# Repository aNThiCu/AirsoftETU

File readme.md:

Latest board is very promising , i have semi-abandoned the idea of separating the controls and power components from the sensors. The board is now a 4 layer consisting of GND-3.3V-GND-GND copper pours.
Pcb manufacturing at home sadly cannot fullfill my needs for this project , future versions will not be able to be manufactured in house as i have finished some of the testing needed for a complete product.

This revision still is in no way usable , as i haven't been able to test any of the new software implementations. I just finished the firmware and i am about to go on with assembling the rest of the PCB.
I've been using a board with no power electronics until now for testing the signal complementarity and overall logic of the system.

Hardware changes made from the last readme update:

 - added back the high side pmos , board cannot function without it as freewheel diode would blow
 - added back the mode selector phototransistors and led-added a schmitt trigger for hardware debounce
 - added proper gate drivers , MCP1416T-E
 - added some ESD protection diodes on the gates of the power FETS and 12v power rail
 - moved leds to the 3.3v rail
 - modified shape of PCB for better fitment

Software changes made from the last readme update:
   - configurable duty cycle, not tested actual usable range , over 90% is considered 100% due to dead_time limitations
   - configurable dead time ticks for pwm , 1 tick = 200ns , good for different types of power mosfets
   - implemented synchronous rectification to take the burden off the flywheel diode 
   - changed driving logic to permit both PWM and on/off
   - added burst mode capability
   - changed to platformio

What's coming next:
   - finishing testing with new pcb and firmware
   - troubleshooting indicators, buzzer for quick configs in the upcoming settings tab
   - folder with everything needed for direct manufacturing from a factory
   - might do a different type of trigger , either optical of magnetic , for longevity sake , i like the clicking feel of microswitches more though
   
What's been marked done from last readme update:
   - configurable mode selector switch with multiple modes
   - redo of shape for better fitment in V2 gearboxes

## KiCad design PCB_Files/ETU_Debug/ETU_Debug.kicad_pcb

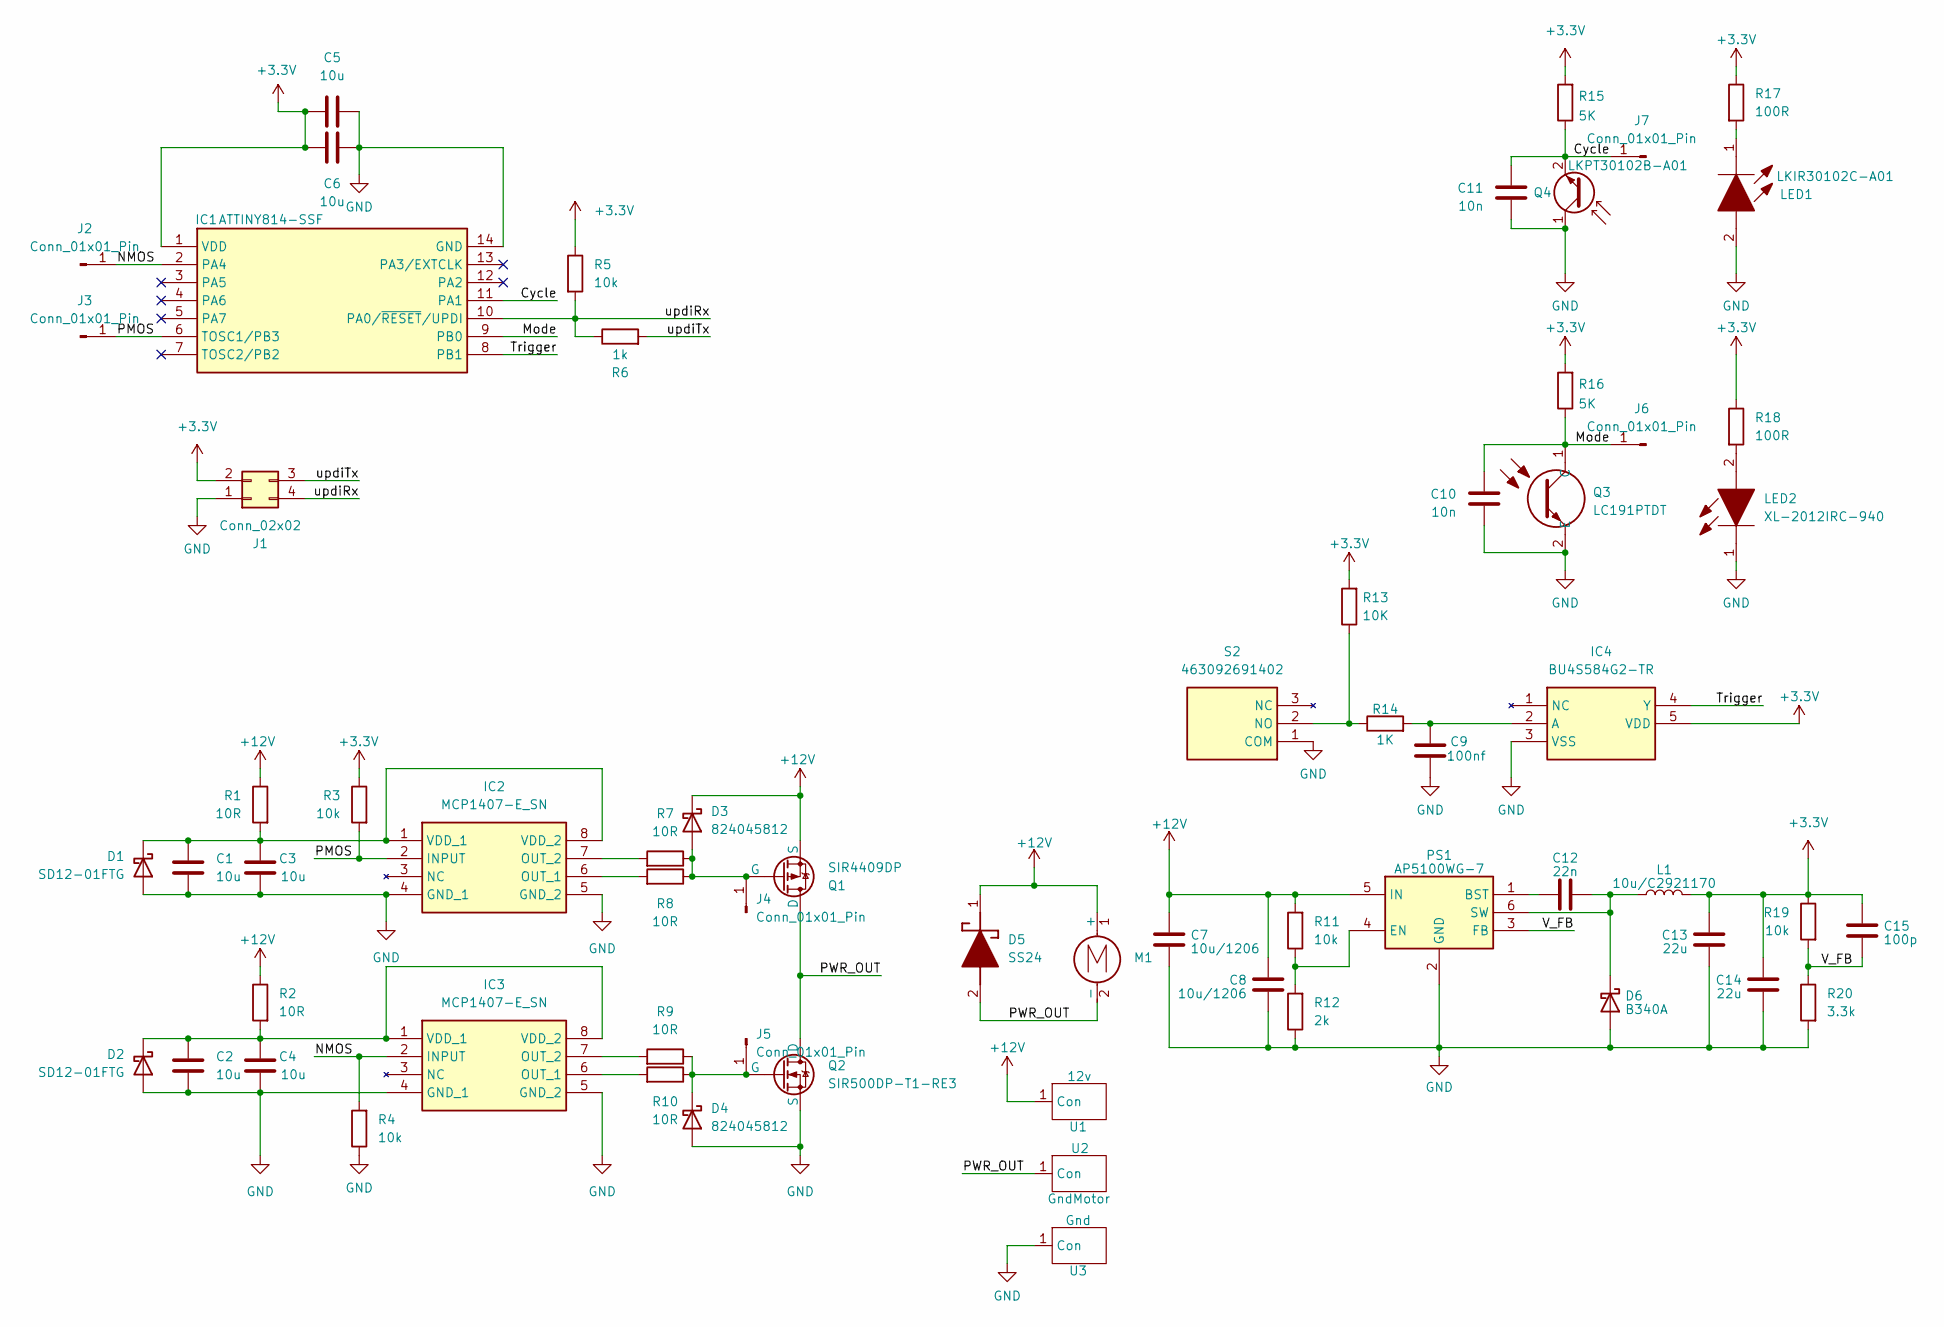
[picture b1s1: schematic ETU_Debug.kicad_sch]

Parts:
C1, C2, C3, C4, C5, C6: 10u; C_0603_1608Metric
C7, C8: 10u/1206; C_0603_1608Metric; MPN C13585
C9: 100nf; C_0603_1608Metric
C10, C11: 10n; C_0603_1608Metric
C12: 22n; C_0603_1608Metric; MPN C21122
C13, C14: 22u; C_0603_1608Metric; MPN C45783
C15: 100p; C_0603_1608Metric; MPN C1790
D1, D2: SD12-01FTG; SOD2613X114N
D3, D4: 824045812
D5: SS24; DIOM5436X247N; Mouser Part Number 821-SS24
D6: B340A; D_SMA; MPN C3018525
IC1: ATTINY814-SSF; SOIC127P600X175-14N; Mouser Part Number 579-ATTINY814-SSF
IC2, IC3: MCP1407-E_SN; SOIC127P600X175-8N; Mouser Part Number 579-MCP1407-E/SN
IC4: BU4S584G2-TR; SOT95P280X125-5N; Mouser Part Number 755-BU4S584G2-TR
J1: Conn_02x02; PinHeader_2x02_P2.54mm_Vertical
J2, J3, J4, J5, J6, J7: Conn_01x01_Pin; PinHeader_1x01_P2.54mm_Vertical
L1: 10u/C2921170; L_Chilisin_BMRA00040420; MPN C2921170
LED1: LKIR30102C-A01; APA3010P3C; Mouser Part Number 755-CSL1501RW1
LED2: XL-2012IRC-940; LEDC2012X105N; Mouser Part Number 604-APTD2012SF4C
M1: Motor_DC
PS1: AP5100WG-7; SOT95P285X140-6N; Mouser Part Number 621-AP5100WG-7
Q1: SIR4409DP; POWERPAKSO-8
Q2: SIR500DP-T1-RE3; POWERPAKSO-8
Q3: LC191PTDT; AP1608P1CP22; Mouser Part Number 604-AP1608P1C-P22
Q4: LKPT30102B-A01; APA3010P3C
R1, R2, R7, R8, R9, R10: 10R; R_0603_1608Metric
R3, R4, R5: 10k; R_0603_1608Metric
R6: 1k; R_0603_1608Metric
R11, R19: 10k; R_0603_1608Metric; MPN C25804
R12: 2k; R_0603_1608Metric; MPN C22975
R13: 10K; R_0603_1608Metric
R14: 1K; R_0603_1608Metric
R15, R16: 5K; R_0603_1608Metric
R17, R18: 100R; R_0603_1608Metric
R20: 3.3k; R_0603_1608Metric; MPN C22975
S2: 463092691402; Mouser Part Number 710-463092691402
U1: 12v; Copper_Pad
U2: GndMotor; Copper_Pad
U3: Gnd; Copper_Pad

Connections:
+3.3V: C5.1, C6.1, C13.1, C14.1, C15.1, IC1.1 (VDD), IC4.5 (VDD), J1.2, L1.2, R3.1, R5.1, R13.2, R15.2, R16.2, R17.1, R18.1, R19.1
+12V: C7.1, C8.1, D3.1 (K), D5.1 (K), M1.1 (+), PS1.5 (IN), Q1.1 (S), Q1.2 (S), Q1.3 (S), R1.1, R2.1, R11.2, U1.1 (Con)
/Cycle: C11.1, IC1.11 (PA1), J7.1, Q4.2 (E), R15.1
/Mode: C10.1, IC1.9 (PB0), J6.1, Q3.1 (C), R16.1
/NMOS: IC1.2 (PA4), IC3.2 (INPUT), J2.1, R4.2
/PMOS: IC1.6 (TOSC1/PB3), IC2.2 (INPUT), J3.1, R3.2
/PWR_OUT: D5.2 (A), M1.2 (-), Q1.5 (D), Q1.6 (D), Q1.7 (D), Q1.8 (D), Q1.9 (D), Q2.5 (D), Q2.6, Q2.7, Q2.8, Q2.9, U2.1 (Con)
/Trigger: IC1.8 (PB1), IC4.4 (Y)
/V_FB: C15.2, PS1.3 (FB), R19.2, R20.1
/updiRx: IC1.10 (PA0/~RESET/UPDI), J1.4, R5.2, R6.1
/updiTx: J1.3, R6.2
GND: C1.2, C2.2, C3.1, C4.1, C5.2, C6.2, C7.2, C8.2, C9.1, C10.2, C11.2, C13.2, C14.2, D1.2 (A), D2.2 (A), D4.2 (A), D6.2 (A), IC1.14 (GND), IC2.4 (GND_1), IC2.5 (GND_2), IC3.4 (GND_1), IC3.5 (GND_2), IC4.3 (VSS), J1.1, LED1.2, LED2.1, PS1.2 (GND), Q2.1 (S), Q2.2, Q2.3, Q3.2 (E), Q4.1 (C), R4.1, R12.1, R20.2, S2.1 (COM), U3.1 (Con)
unnamed: C1.1, C3.2, D1.1 (K), IC2.1 (VDD_1), IC2.8 (VDD_2), R1.2
unnamed: C2.1, C4.2, D2.1 (K), IC3.1 (VDD_1), IC3.8 (VDD_2), R2.2
unnamed: D3.2 (A), J4.1, Q1.4 (G), R7.1, R8.1
unnamed: D4.1 (K), J5.1, Q2.4 (G), R9.1, R10.1
unnamed: C12.2, D6.1 (K), L1.1, PS1.6 (SW)
unnamed: IC2.6 (OUT_1), R8.2
unnamed: IC2.7 (OUT_2), R7.2
unnamed: IC3.6 (OUT_1), R10.2
unnamed: IC3.7 (OUT_2), R9.2
unnamed: C9.2, IC4.2 (A), R14.2
unnamed: LED1.1, R17.2
unnamed: LED2.2, R18.2
unnamed: C12.1, PS1.1 (BST)
unnamed: PS1.4 (EN), R11.1, R12.2
unnamed: R13.1, R14.1, S2.2 (NO)

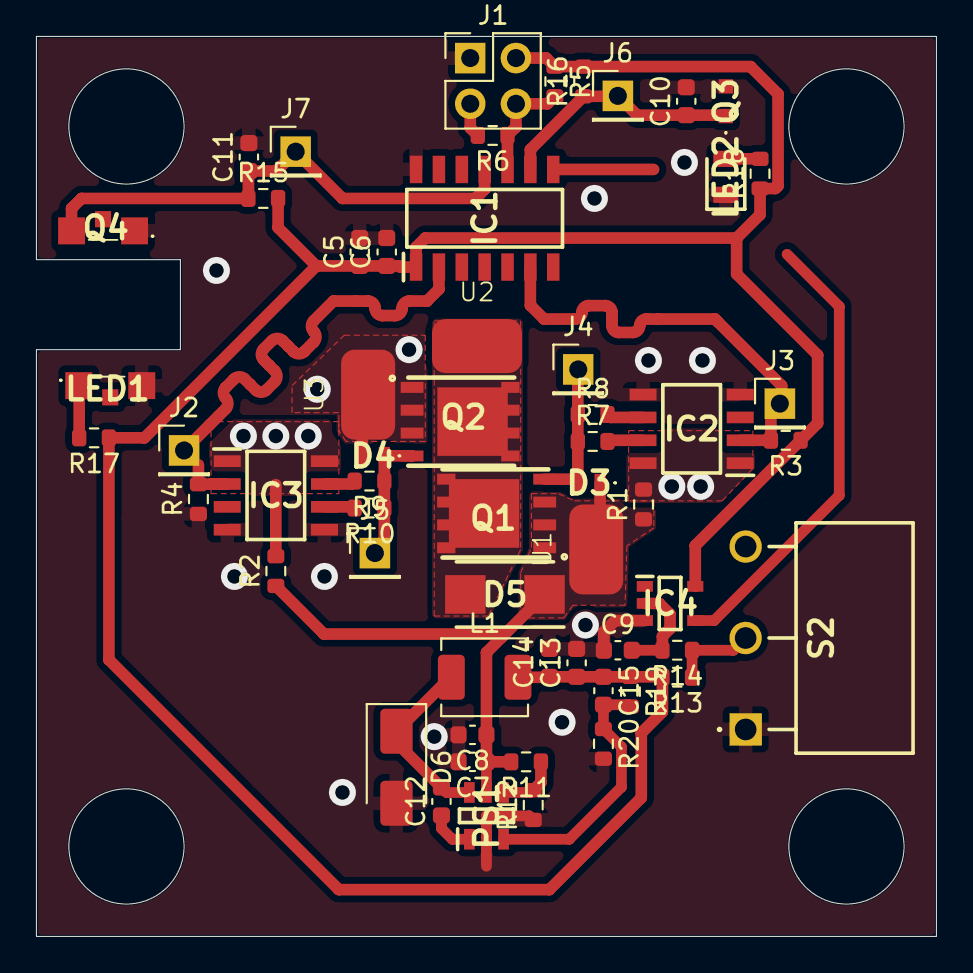
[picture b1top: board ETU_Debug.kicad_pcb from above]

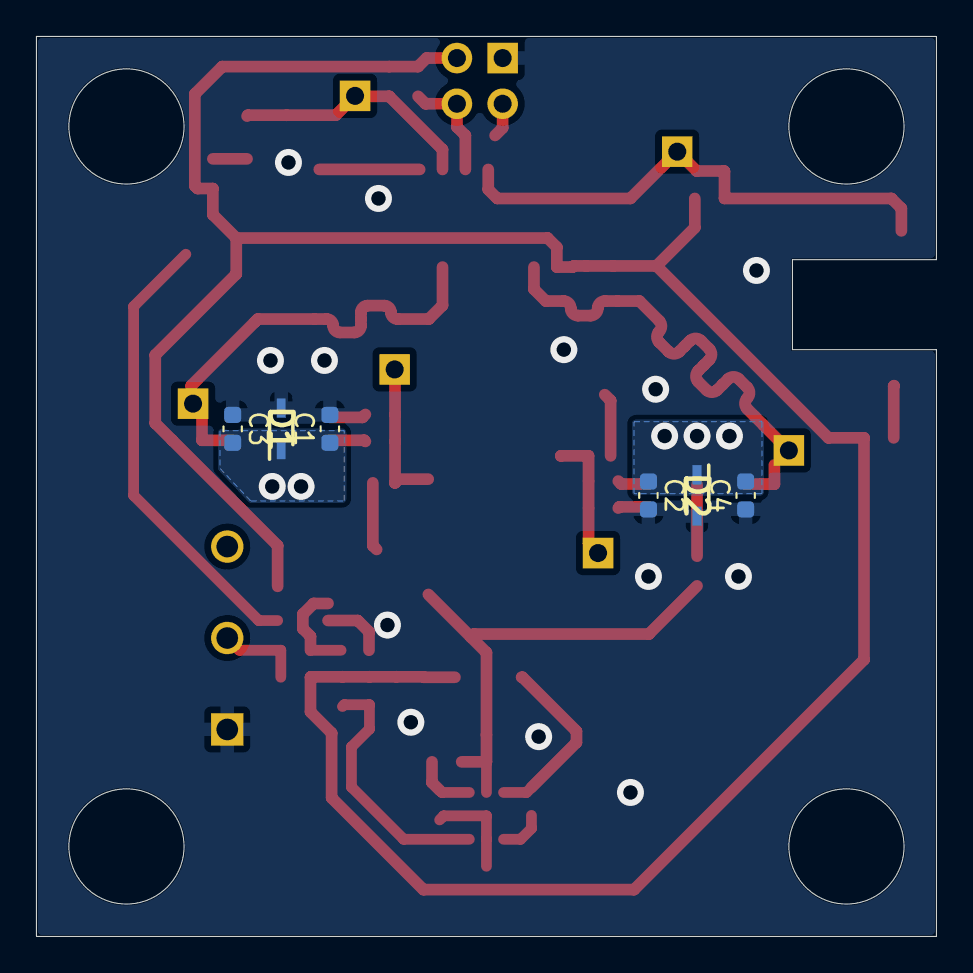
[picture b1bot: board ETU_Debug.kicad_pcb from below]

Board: 2 copper layers, 50.0 x 50.0 mm, 64 parts (6 on the bottom side), 27 nets.

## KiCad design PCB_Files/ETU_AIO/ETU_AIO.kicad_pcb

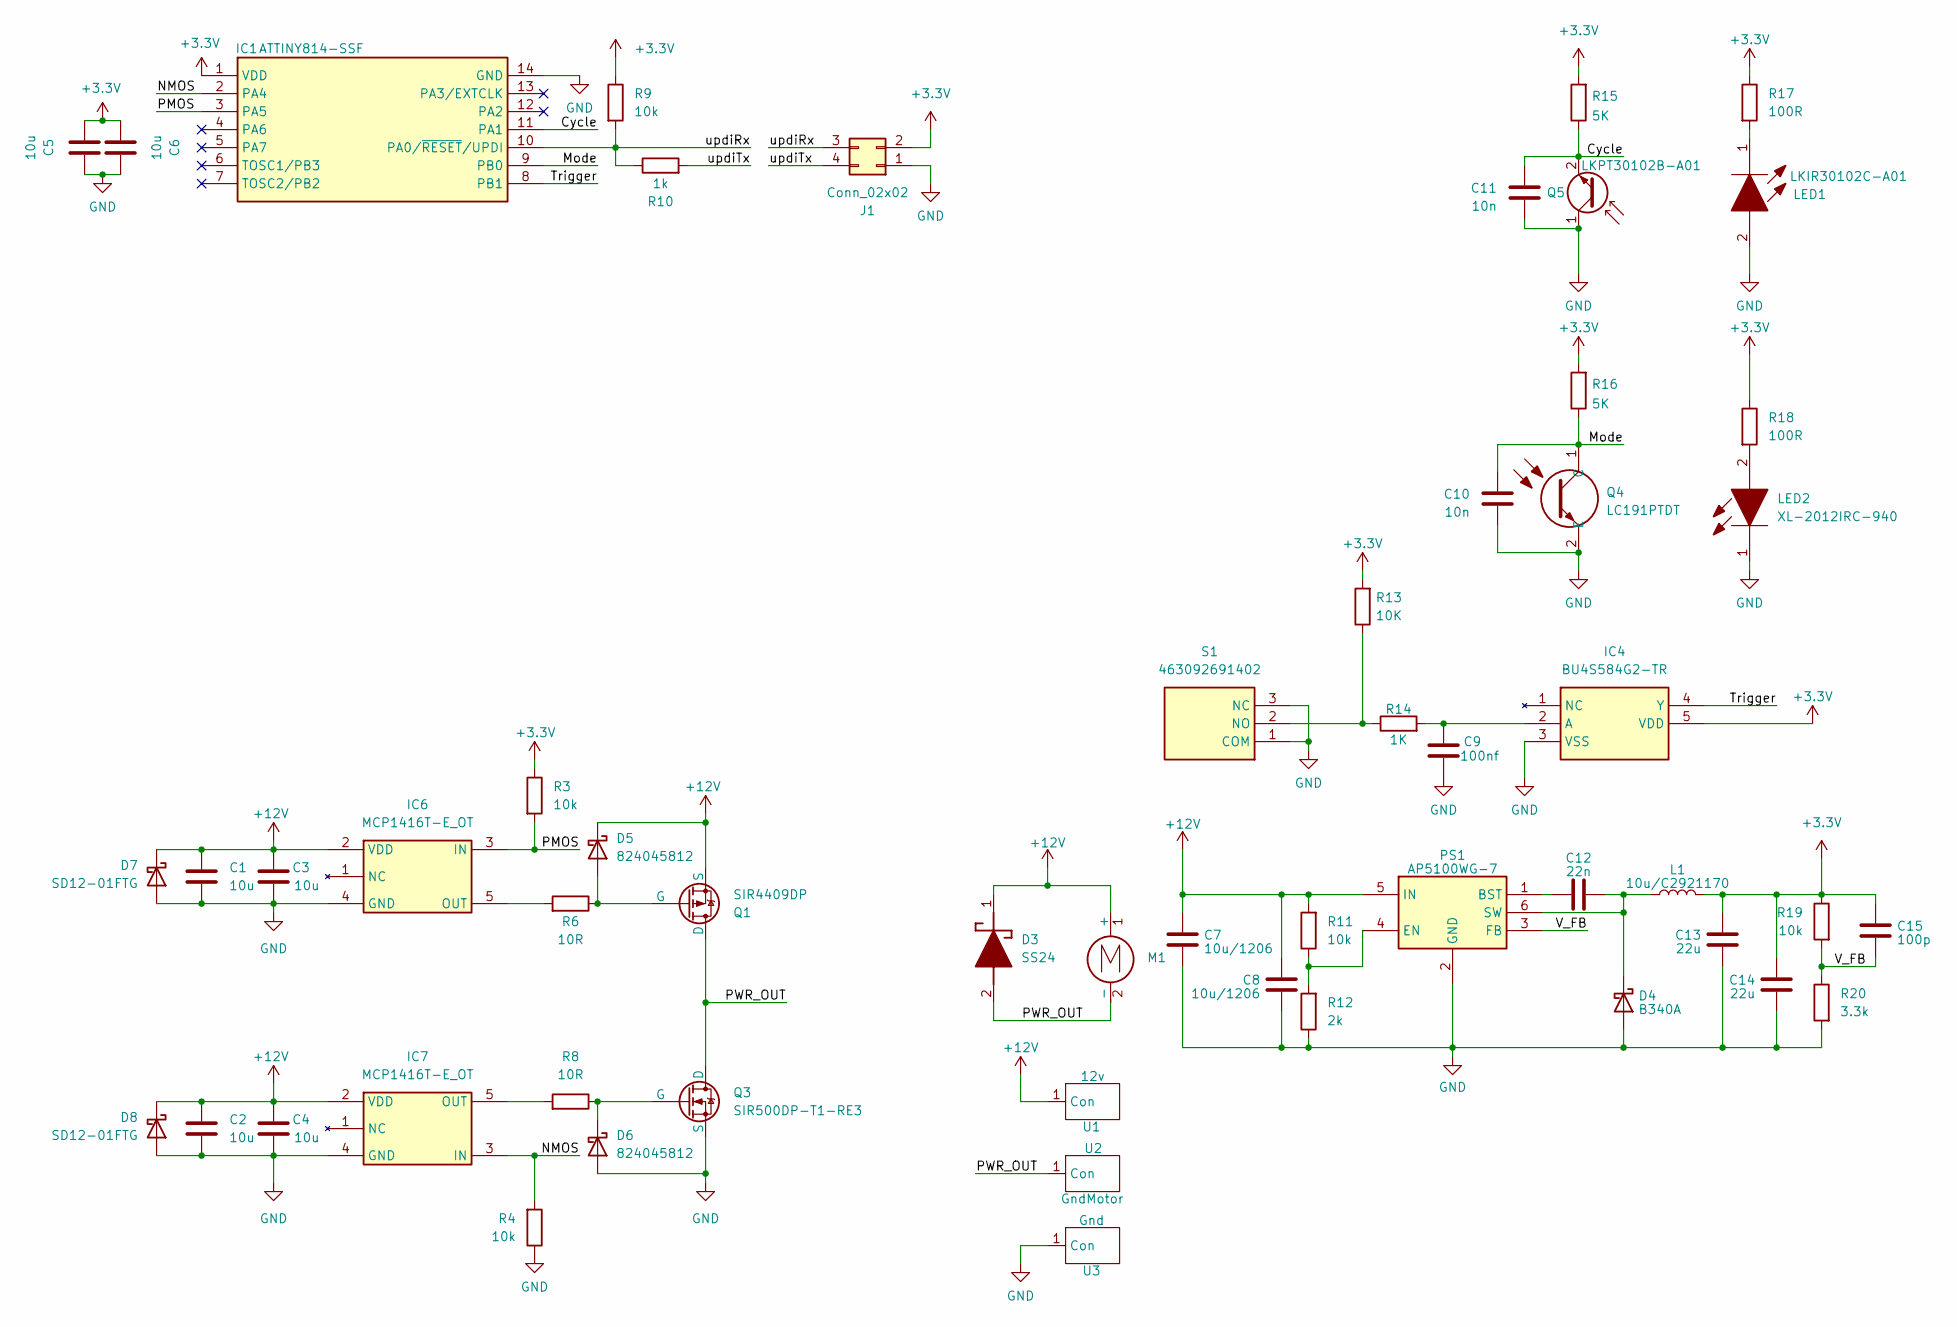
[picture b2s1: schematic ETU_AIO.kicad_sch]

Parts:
C1, C2, C3, C4, C5, C6: 10u; C_0603_1608Metric
C7, C8: 10u/1206; C_0603_1608Metric; MPN C13585
C9: 100nf; C_0603_1608Metric
C10, C11: 10n; C_0603_1608Metric
C12: 22n; C_0603_1608Metric; MPN C21122
C13, C14: 22u; C_0603_1608Metric; MPN C45783
C15: 100p; C_0603_1608Metric; MPN C1790
D3: SS24; DIOM5436X247N; Mouser Part Number 821-SS24
D4: B340A; D_SMA; MPN C3018525
D5, D6: 824045812
D7, D8: SD12-01FTG; SOD2613X114N
IC1: ATTINY814-SSF; SOIC127P600X175-14N; Mouser Part Number 579-ATTINY814-SSF
IC4: BU4S584G2-TR; SOT95P280X125-5N; Mouser Part Number 755-BU4S584G2-TR
IC6, IC7: MCP1416T-E_OT; SOT95P270X145-5N; Mouser Part Number 579-MCP1416T-E/OT
J1: Conn_02x02; PinHeader_1x04_P2.54mm_Vertical
L1: 10u/C2921170; L_Chilisin_BMRA00040420; MPN C2921170
LED1: LKIR30102C-A01; APA3010P3C; Mouser Part Number 755-CSL1501RW1
LED2: XL-2012IRC-940; LEDC2012X105N; Mouser Part Number 604-APTD2012SF4C
M1: Motor_DC
PS1: AP5100WG-7; SOT95P285X140-6N; Mouser Part Number 621-AP5100WG-7
Q1: SIR4409DP; POWERPAKSO-8
Q3: SIR500DP-T1-RE3; POWERPAKSO-8
Q4: LC191PTDT; AP1608P1CP22; Mouser Part Number 604-AP1608P1C-P22
Q5: LKPT30102B-A01; APA3010P3C
R3, R4, R9: 10k; R_0603_1608Metric
R6, R8: 10R; R_0603_1608Metric
R10: 1k; R_0603_1608Metric
R11, R19: 10k; R_0603_1608Metric; MPN C25804
R12: 2k; R_0603_1608Metric; MPN C22975
R13: 10K; R_0603_1608Metric
R14: 1K; R_0603_1608Metric
R15, R16: 5K; R_0603_1608Metric
R17, R18: 100R; R_0603_1608Metric
R20: 3.3k; R_0603_1608Metric; MPN C22975
S1: 463092691402; Mouser Part Number 710-463092691402
U1: 12v; Copper_Pad
U2: GndMotor; Copper_Pad
U3: Gnd; Copper_Pad

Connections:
+3.3V: C5.1, C6.1, C13.1, C14.1, C15.1, IC1.1 (VDD), IC4.5 (VDD), J1.2, L1.2, R3.1, R9.1, R13.2, R15.2, R16.2, R17.1, R18.1, R19.1
+12V: C1.1, C2.1, C3.2, C4.2, C7.1, C8.1, D3.1 (K), D5.1 (K), D7.1 (K), D8.1 (K), IC6.2 (VDD), IC7.2 (VDD), M1.1 (+), PS1.5 (IN), Q1.1 (S), Q1.2 (S), Q1.3 (S), R11.2, U1.1 (Con_1)
/Cycle: C11.1, IC1.11 (PA1), Q5.2 (E), R15.1
/Mode: C10.1, IC1.9 (PB0), Q4.1 (C), R16.1
/NMOS: IC1.2 (PA4), IC7.3 (IN), R4.2
/PMOS: IC1.3 (PA5), IC6.3 (IN), R3.2
/PWR_OUT: D3.2 (A), M1.2 (-), Q1.5 (D), Q1.6 (D), Q1.7 (D), Q1.8 (D), Q1.9 (D), Q3.5 (D), Q3.6, Q3.7, Q3.8, Q3.9, U2.1 (Con_1)
/Trigger: IC1.8 (PB1), IC4.4 (Y)
/V_FB: C15.2, PS1.3 (FB), R19.2, R20.1
/updiRx: IC1.10 (PA0/~RESET/UPDI), J1.3, R9.2, R10.1
/updiTx: J1.4, R10.2
GND: C1.2, C2.2, C3.1, C4.1, C5.2, C6.2, C7.2, C8.2, C9.1, C10.2, C11.2, C13.2, C14.2, D4.2 (A), D6.2 (A), D7.2 (A), D8.2 (A), IC1.14 (GND), IC4.3 (VSS), IC6.4 (GND), IC7.4 (GND), J1.1, LED1.2, LED2.1, PS1.2 (GND), Q3.1 (S), Q3.2, Q3.3, Q4.2 (E), Q5.1 (C), R4.1, R12.1, R20.2, S1.1 (COM), S1.3 (NC), U3.1 (Con_1)
unnamed: C12.2, D4.1 (K), L1.1, PS1.6 (SW)
unnamed: D5.2 (A), Q1.4 (G), R6.1
unnamed: D6.1 (K), Q3.4 (G), R8.1
unnamed: C9.2, IC4.2 (A), R14.2
unnamed: IC6.5 (OUT), R6.2
unnamed: IC7.5 (OUT), R8.2
unnamed: LED1.1, R17.2
unnamed: LED2.2, R18.2
unnamed: C12.1, PS1.1 (BST)
unnamed: PS1.4 (EN), R11.1, R12.2
unnamed: R13.1, R14.1, S1.2 (NO)

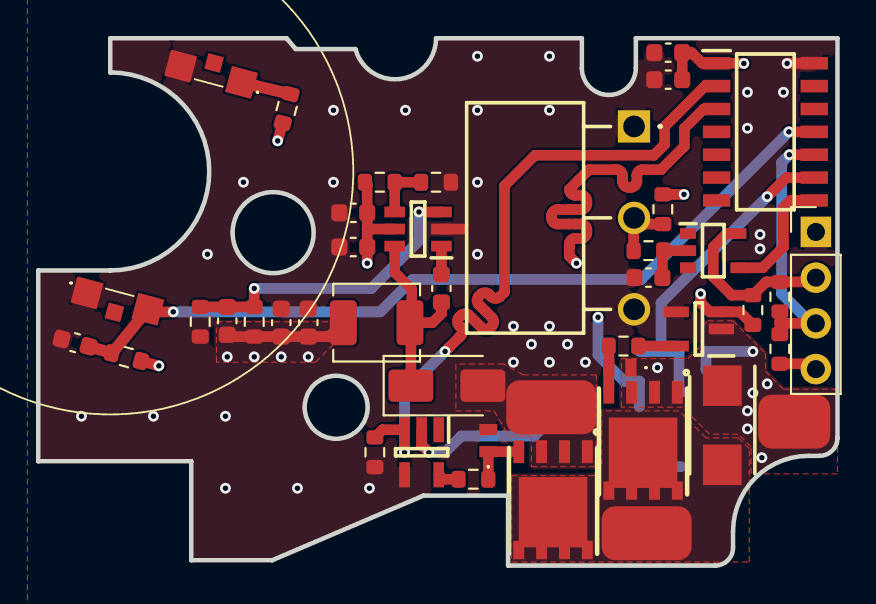
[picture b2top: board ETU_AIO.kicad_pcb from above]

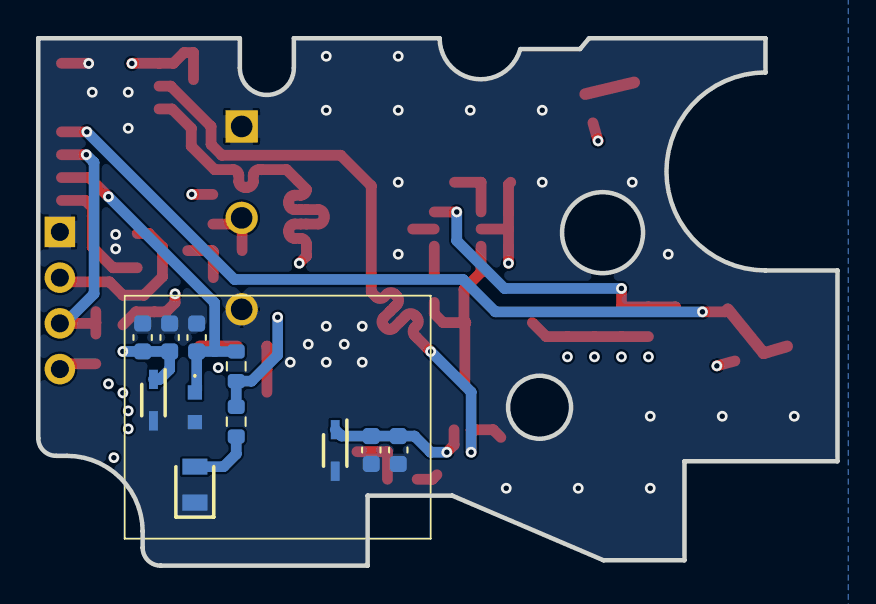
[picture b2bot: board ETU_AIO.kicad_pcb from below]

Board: 4 copper layers, 44.4 x 29.3 mm, 54 parts (11 on the bottom side), 23 nets.

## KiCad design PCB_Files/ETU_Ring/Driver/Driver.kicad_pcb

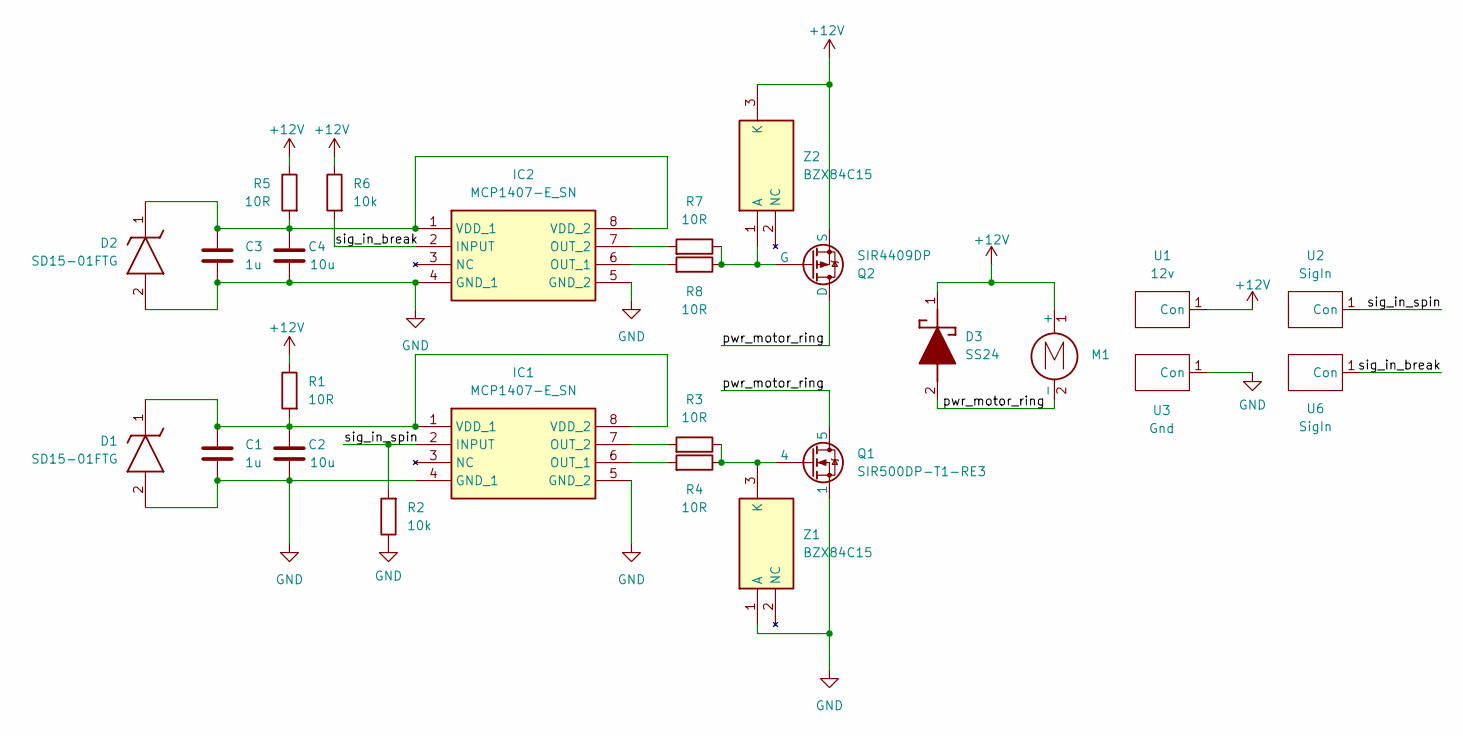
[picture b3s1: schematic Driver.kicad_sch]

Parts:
C1, C3: 1u; C_0603_1608Metric
C2, C4: 10u; C_0603_1608Metric
D1, D2: SD15-01FTG; SOD2613X114N; Manufacturer_Part_Number SD15-01FTG
D3: SS24; DIOM5436X247N; Mouser Part Number 821-SS24
IC1, IC2: MCP1407-E_SN; SOIC127P600X175-8N; Mouser Part Number 579-MCP1407-E/SN
M1: Motor_DC
Q1: SIR500DP-T1-RE3; POWERPAKSO-8
Q2: SIR4409DP; POWERPAKSO-8
R1, R3, R4, R5, R7, R8: 10R; R_0603_1608Metric
R2, R6: 10k; R_0603_1608Metric
U1: 12v; Copper_Pad
U2, U6: SigIn; Copper_Pad
U3: Gnd; Copper_Pad
Z1, Z2: BZX84C15; SOT96P260X140-3N; Manufacturer_Part_Number BZX84C15

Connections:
+12V: D3.1 (K), M1.1 (+), Q2.1 (S), Q2.2 (S), Q2.3 (S), R1.1, R5.1, R6.1, U1.1 (Con), Z2.2 (NC), Z2.3 (K)
/pwr_motor_ring: D3.2 (A), M1.2 (-), Q1.5, Q1.6, Q1.7, Q1.8, Q1.9, Q2.5 (D), Q2.6 (D), Q2.7 (D), Q2.8 (D), Q2.9 (D)
/sig_in_break: IC2.2 (INPUT), R6.2, U6.1 (Con)
/sig_in_spin: IC1.2 (INPUT), R2.2, U2.1 (Con)
GND: C1.2, C2.1, C3.2, C4.1, D1.2 (A), D2.2 (A), IC1.4 (GND_1), IC1.5 (GND_2), IC2.4 (GND_1), IC2.5 (GND_2), Q1.1, Q1.2, Q1.3, R2.1, U3.1 (Con), Z1.1 (A)
unnamed: C1.1, C2.2, D1.1 (K), IC1.1 (VDD_1), IC1.8 (VDD_2), R1.2
unnamed: C3.1, C4.2, D2.1 (K), IC2.1 (VDD_1), IC2.8 (VDD_2), R5.2
unnamed: IC1.6 (OUT_1), R4.2
unnamed: IC1.7 (OUT_2), R3.2
unnamed: IC2.6 (OUT_1), R8.2
unnamed: IC2.7 (OUT_2), R7.2
unnamed: Q2.4 (G), R7.1, R8.1, Z2.1 (A)
unnamed: Q1.4, R3.1, R4.1, Z1.3 (K)

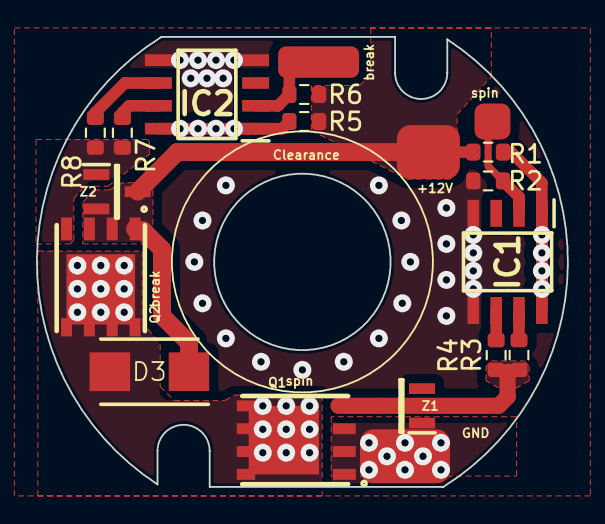
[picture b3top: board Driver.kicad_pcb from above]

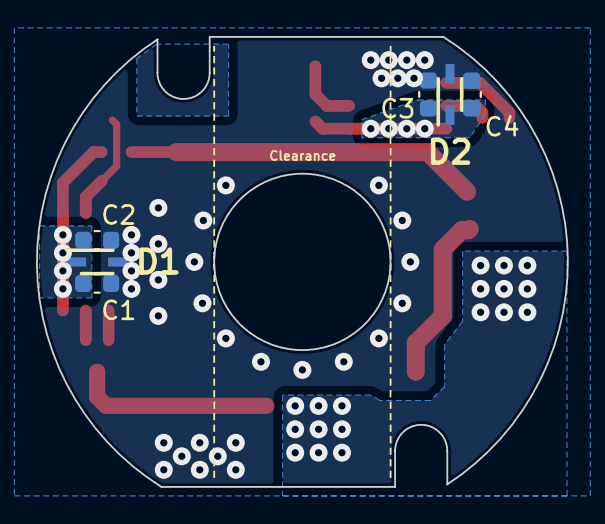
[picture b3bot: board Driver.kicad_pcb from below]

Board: 2 copper layers, 29.5 x 25.0 mm, 25 parts (6 on the bottom side), 13 nets.

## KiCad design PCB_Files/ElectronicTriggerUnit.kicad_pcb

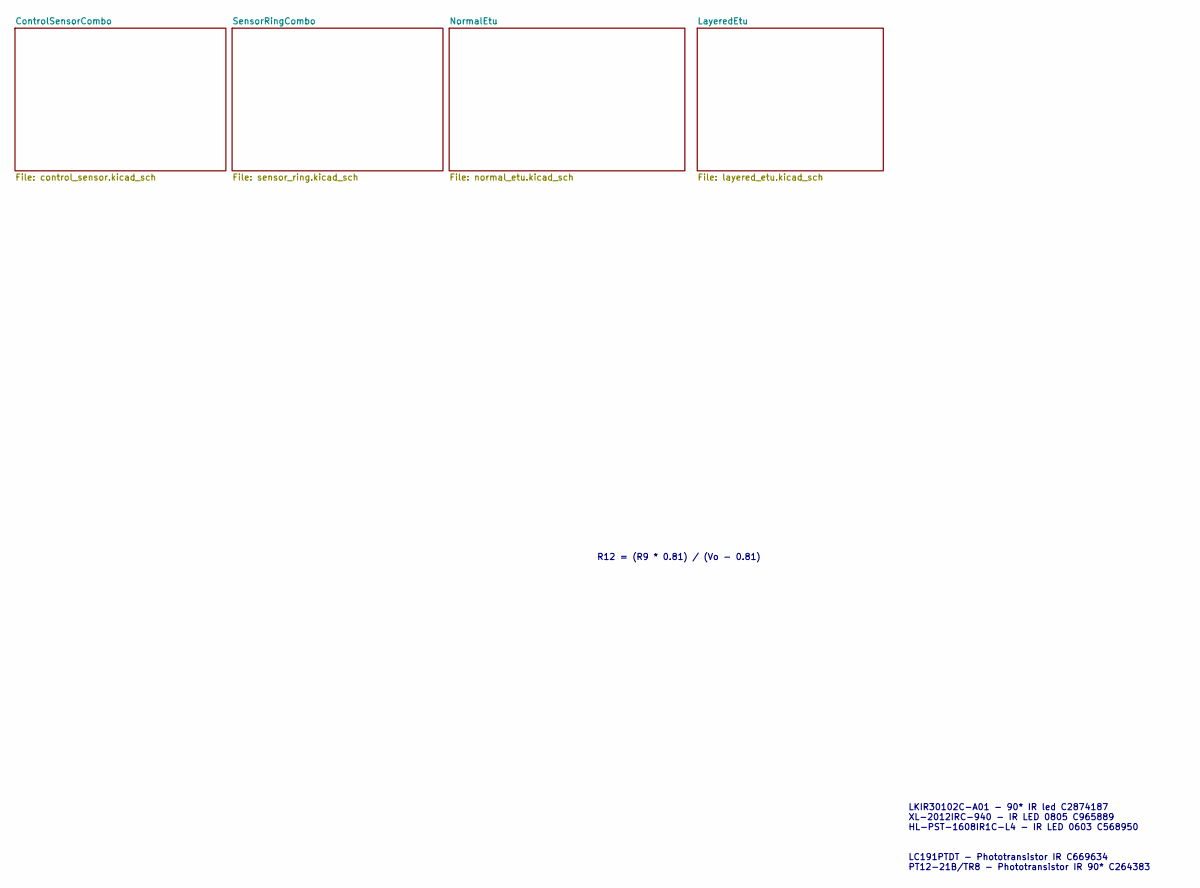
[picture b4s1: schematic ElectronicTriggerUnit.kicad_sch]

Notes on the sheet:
R12 = (R9 * 0.81) / (Vo - 0.81)
LKIR30102C-A01 - 90* IR led C2874187 XL-2012IRC-940 - IR LED 0805 C965889 HL-PST-1608IR1C-L4 - IR LED 0603 C568950 LC191PTDT - Phototransistor IR C669634 PT12-21B/TR8 - Phototransistor IR 90* C264383

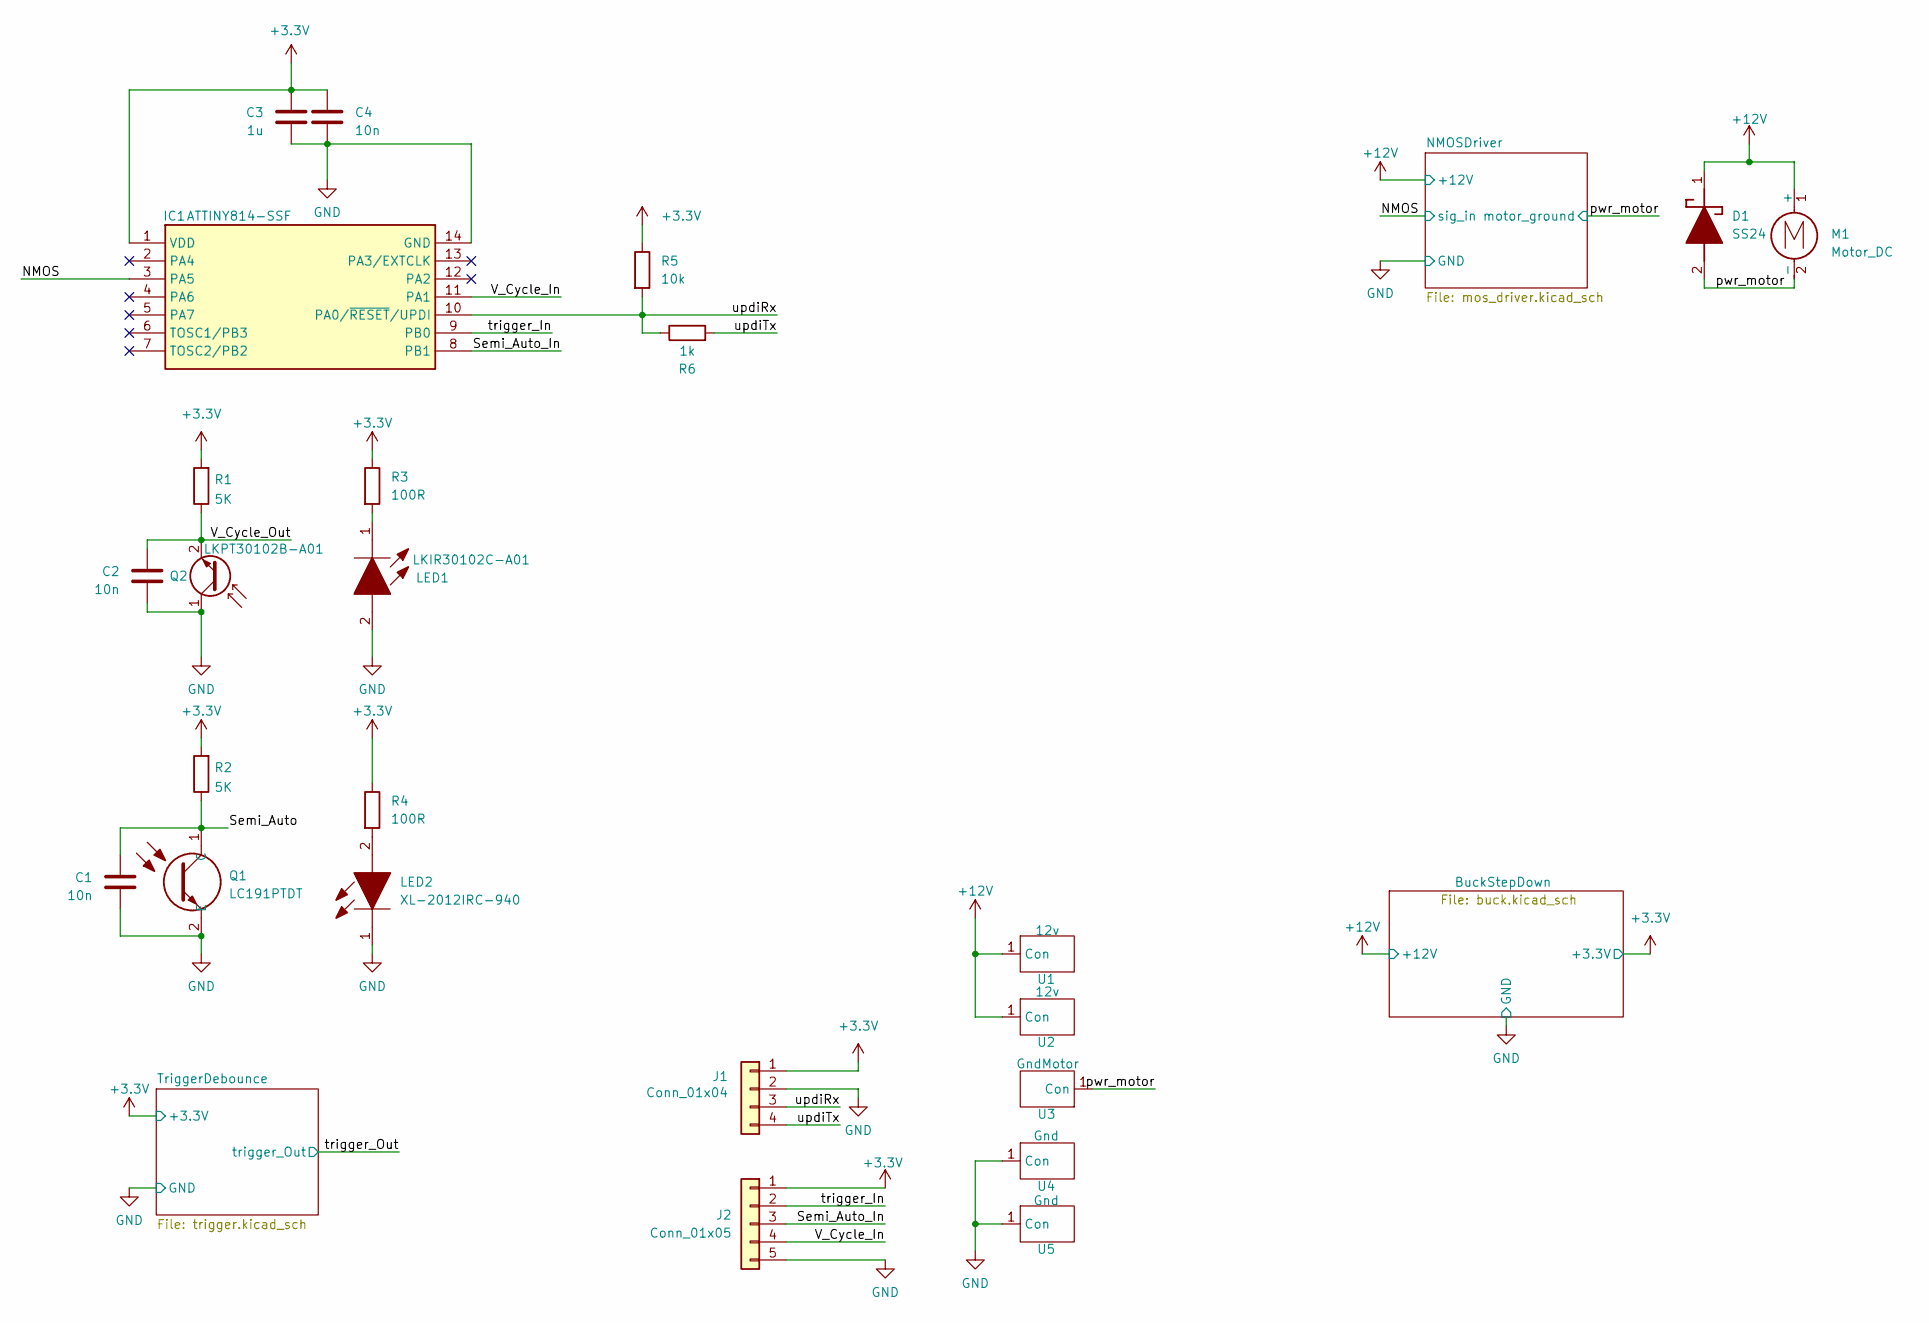
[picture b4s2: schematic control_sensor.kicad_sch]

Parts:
C1, C2, C4: 10n; C_0603_1608Metric
C3: 1u; C_0603_1608Metric
D1: SS24; DIOM5436X247N; Mouser Part Number 821-SS24
IC1: ATTINY814-SSF; SOIC127P600X175-14N; Mouser Part Number 579-ATTINY814-SSF
J1: Conn_01x04; PinHeader_1x04_P2.54mm_Vertical
J2: Conn_01x05; PinSocket_1x05_P2.54mm_Vertical
LED1: LKIR30102C-A01; APA3010P3C; Mouser Part Number 755-CSL1501RW1
LED2: XL-2012IRC-940; LEDC2012X105N; Mouser Part Number 604-APTD2012SF4C
M1: Motor_DC
Q1: LC191PTDT; AP1608P1CP22; Mouser Part Number 604-AP1608P1C-P22
Q2: LKPT30102B-A01; APA3010P3C
R1, R2: 5K; R_0603_1608Metric
R3, R4: 100R; R_0603_1608Metric
R5: 10k; R_0603_1608Metric
R6: 1k; R_0603_1608Metric
U1, U2: 12v; Copper_Pad
U3: GndMotor; Copper_Pad
U4, U5: Gnd; Copper_Pad

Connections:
+3.3V: C3.1, C4.1, IC1.1 (VDD), J1.1, J2.1, R1.2, R2.2, R3.1, R4.1, R5.1; also elsewhere on the board
+12V: D1.1 (K), M1.1 (+), U1.1 (Con), U2.1 (Con); also elsewhere on the board
/ControlSensorCombo/NMOS: IC1.3 (PA5); also elsewhere on the board
/ControlSensorCombo/Semi_Auto: C1.1, Q1.1 (C), R2.1
/ControlSensorCombo/Semi_Auto_In: IC1.8 (PB1), J2.3
/ControlSensorCombo/V_Cycle_In: IC1.11 (PA1), J2.4
/ControlSensorCombo/V_Cycle_Out: C2.1, Q2.2 (E), R1.1
/ControlSensorCombo/pwr_motor: D1.2 (A), M1.2 (-), U3.1 (Con); also elsewhere on the board
/ControlSensorCombo/trigger_In: IC1.9 (PB0), J2.2
/ControlSensorCombo/updiRx: IC1.10 (PA0/~RESET/UPDI), J1.3, R5.2, R6.1
/ControlSensorCombo/updiTx: J1.4, R6.2
GND: C1.2, C2.2, C3.2, C4.2, IC1.14 (GND), J1.2, J2.5, LED1.2, LED2.1, Q1.2 (E), Q2.1 (C), U4.1 (Con), U5.1 (Con); also elsewhere on the board
unnamed: LED1.1, R3.2
unnamed: LED2.2, R4.2
